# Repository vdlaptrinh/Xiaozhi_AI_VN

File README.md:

# Xiaozhi AI VN (`Xiaozhi_AI_VN`)

Kho lưu trữ mã nguồn, phần cứng và hướng dẫn cấu hình để tự build **Xiaozhi AI** phiên bản tiếng Việt sử dụng vi điều khiển ESP32-S3.

---

## 📂 Cấu trúc Repository

```text
Xiaozhi_AI_VN/
├── esp32s3_kit/         # Thiết kế phần cứng (KiCAD 10 project, có sẵn file xuất PCB PDF)
├── firmware/            # Chứa các file binary (.bin) biên dịch sẵn cho từng loại board
├── huong-dan-build-xiaozhi.md            # Hướng dẫn build xiaozhi
└── README.md            # Tài liệu giới thiệu dự án
```
---

1. Thư mục esp32s3_kit/
Phần cứng thiết kế: Dự án mạch phần cứng dùng KiCAD (phiên bản 10).

Tài liệu sản xuất: Đã hỗ trợ sẵn các file xuất PCB dưới dạng PDF giúp dễ dàng xem xét, in ấn hoặc đặt mạch (Gerber/PCB layout).

2. Thư mục firmware/
File Binary: Tổng hợp các file .bin sẵn sàng để flash trực tiếp lên các dòng board ESP32 hỗ trợ dự án.

Giúp người dùng có thể trải nghiệm nhanh chóng mà chưa cần tự build mã nguồn từ đầu.

🚀 File Hướng dẫn Build Firmware [click here](https://github.com/vdlaptrinh/Xiaozhi_AI_VN/blob/main/huong-dan-build-xiaozhi.md)
Chi tiết từng bước cách tự build firmware Xiaozhi AI tiếng Việt:

[X] Cài đặt môi trường phát triển (ESP-IDF / PlatformIO).

[X] Cấu hình kết nối Audio (I2S, Micro, Loa) và Wi-Fi/Server AI.

[X] Tiến hành biên dịch và nạp firmware (flash) vào ESP32-S3.

🤝 Đóng góp & Phát triển
Mọi đóng góp, báo lỗi (issue) hoặc thảo luận cải tiến phần cứng/phần mềm đều được hoan nghênh để hoàn thiện cộng đồng Xiaozhi AI tại Việt Nam!

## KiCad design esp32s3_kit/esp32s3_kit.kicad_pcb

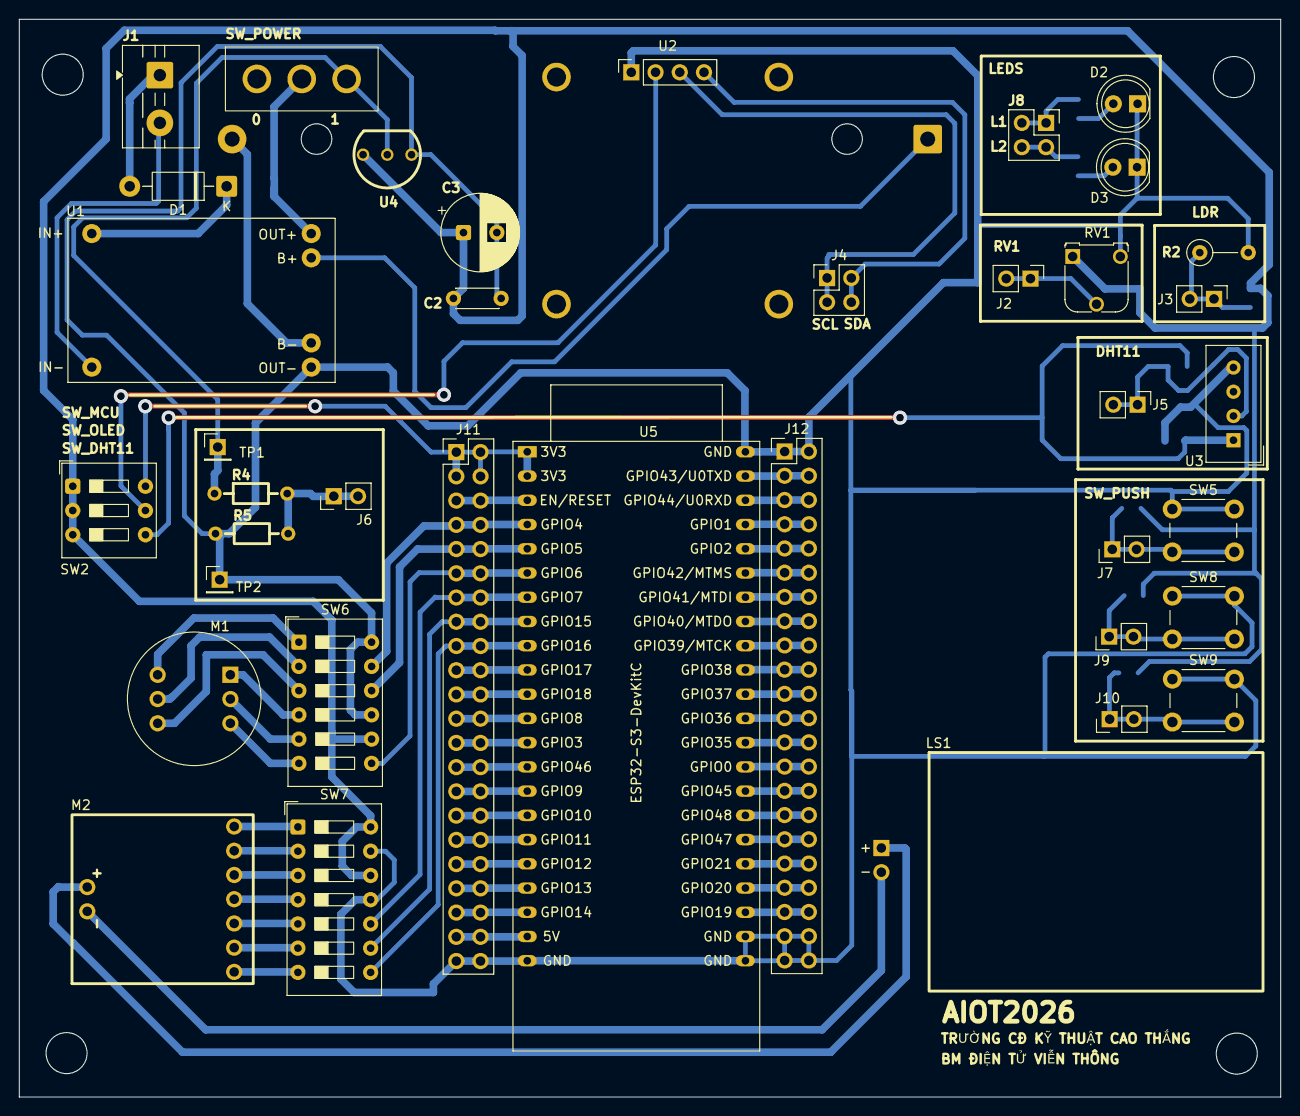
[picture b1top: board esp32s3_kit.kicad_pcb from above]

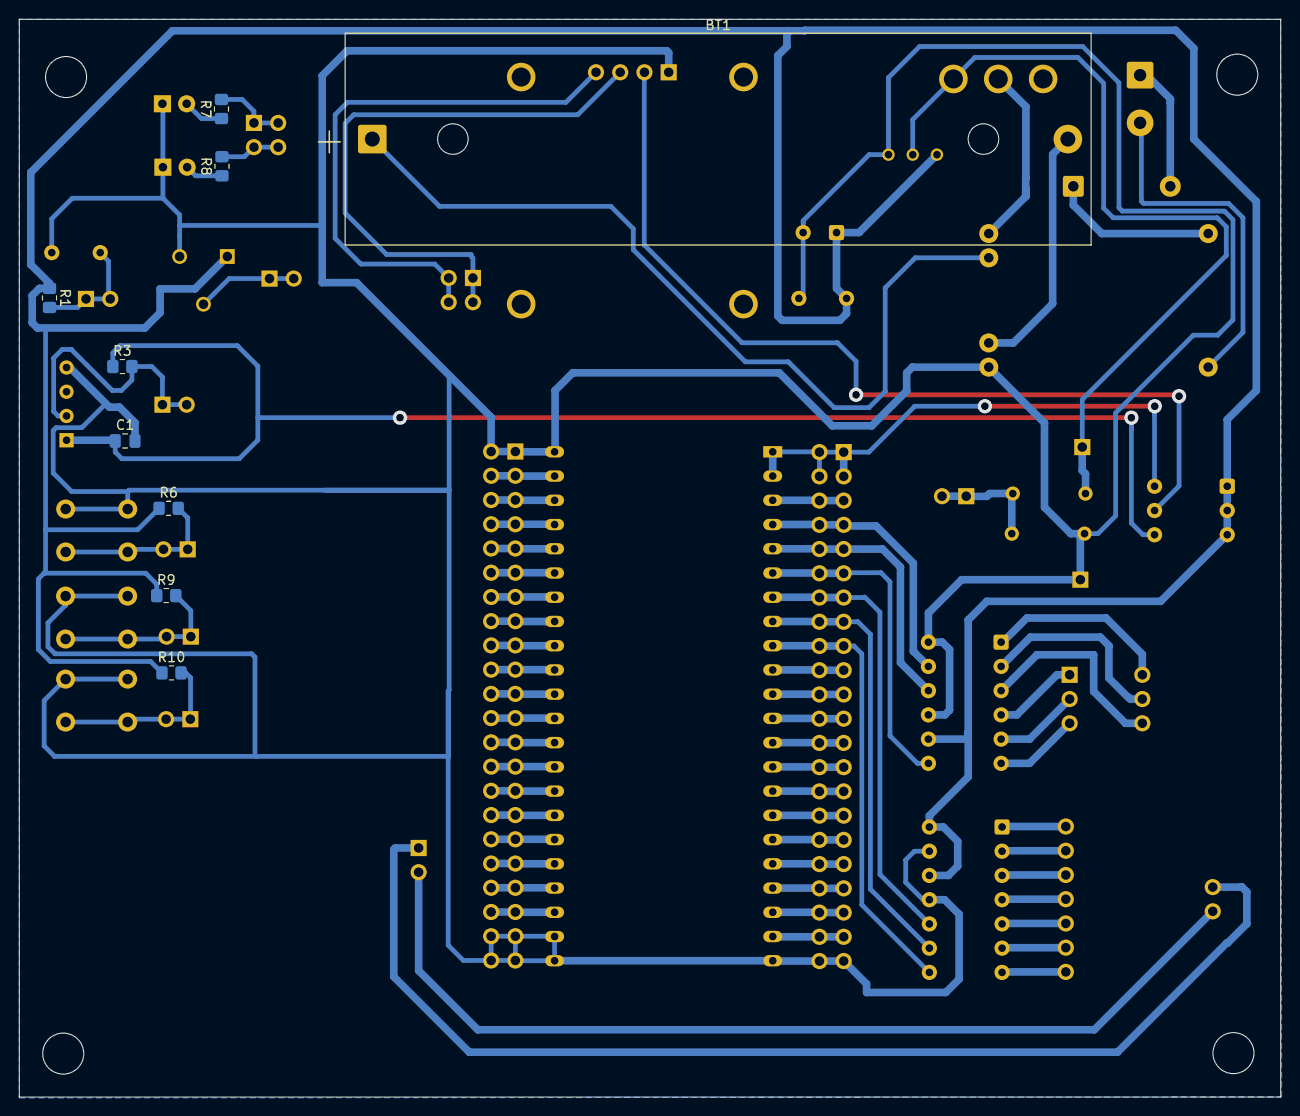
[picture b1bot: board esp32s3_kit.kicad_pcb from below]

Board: 2 copper layers, 132.2 x 112.9 mm, 47 parts (9 on the bottom side), 78 nets.

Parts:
BT1: Battery_Cell; BatteryHolder_MPD_BK-18650-PC2
C1: C; C_0805_2012Metric_Pad1.18x1.45mm_HandSolder
C2: C; C_Disc_D4.3mm_W1.9mm_P5.00mm
C3: C_US; CP_Radial_D8.0mm_P3.50mm
D1: 1N4001; D_DO-41_SOD81_P10.16mm_Horizontal
D2, D3: LED; LED_D5.0mm
J1: Screw_Terminal_01x02; TerminalBlock_MaiXu_MX126-5.0-02P_1x02_P5.00mm
J2, J3, J5, J6, J7, J9, J10: Conn_02x01; PinHeader_1x02_P2.54mm_Vertical
J4, J8: Conn_02x02_Top_Bottom; PinHeader_2x02_P2.54mm_Vertical
J11, J12: Conn_02x22_Top_Bottom; PinHeader_2x22_P2.54mm_Vertical_double
LS1: Speaker; speaker_2.5x3.5cm
M1: module_micro_inmp441; MODULE_MICRO_INMP441
M2: Module_MAX98357A
R1, R3, R6, R7, R8, R9, R10: R_US; R_0805_2012Metric_Pad1.20x1.40mm_HandSolder
R2: R_Photo; R_Axial_DIN0207_L6.3mm_D2.5mm_P5.08mm_Vertical
R4, R5: R_US; CFR25S
RV1: R_Potentiometer; Potentiometer_Runtron_RM-065_Vertical
SW1: SW_Wuerth_450301014042; SW_ss12d10
SW2: SW_DIP_x03; SW_DIP_SPSTx03_Slide_9.78x9.8mm_W7.62mm_P2.54mm
SW5, SW8, SW9: SW_Push; SW_PUSH_6mm_H7.3mm
SW6: SW_DIP_x06; SW_DIP_SPSTx06_Slide_9.78x17.42mm_W7.62mm_P2.54mm
SW7: SW_DIP_x07; SW_DIP_SPSTx07_Slide_9.78x19.96mm_W7.62mm_P2.54mm
TP1, TP2: TestPoint; PinHeader_1x01_P2.54mm_Vertical
U1: Module_TP4056; TP4056-Module
U2: Module_OLED_0.96; OLED_SSD1306_I2C_0.96
U3: DHT11; Aosong_DHT11_5.5x12.0_P2.54mm
U4: MCP1700x-330xxTO; 2SC1815_TO_92
U5: ESP32-S3-DevKitC

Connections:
+3V3: C2.1, C3.1, R1.1, R6.1, R9.1, R10.1, RV1.1, SW2.1, SW2.2, SW2.3, SW6.8, SW7.12, SW7.14, U4.3 (VO)
/5V: J11.21, J11.43, U5.21 (5V)
/DHT11: C1.1, R3.1, SW2.4, U3.1 (VDD)
/GPIO0: J12.14, J12.36, U5.31 (GPIO0)
/GPIO1: J12.4, J12.26, U5.41 (GPIO1/ADC1_CH0)
/GPIO2: J12.5, J12.27, U5.40 (GPIO2/ADC1_CH1)
/GPIO3: J11.13, J11.35, U5.13 (GPIO3/ADC1_CH2)
/GPIO4: J11.4, J11.26, SW6.11, U5.4 (GPIO4/ADC1_CH3)
/GPIO5: J11.5, J11.27, SW6.10, U5.5 (GPIO5/ADC1_CH4)
/GPIO6: J11.6, J11.28, SW6.7, U5.6 (GPIO6/ADC1_CH5)
/GPIO7: J11.7, J11.29, SW7.10, U5.7 (GPIO7/ADC1_CH6)
/GPIO8: J11.12, J11.34, U5.12 (GPIO8/ADC1_CH7)
/GPIO9: J11.15, J11.37, U5.15 (GPIO9/ADC1_CH8)
/GPIO10: J11.16, J11.38, U5.16 (GPIO10/ADC1_CH9)
/GPIO11: J11.17, J11.39, U5.17 (GPIO11/ADC2_CH0)
/GPIO12: J11.18, J11.40, U5.18 (GPIO12/ADC2_CH1)
/GPIO13: J11.19, J11.41, U5.19 (GPIO13/ADC2_CH2)
/GPIO14: J11.20, J11.42, U5.20 (GPIO14/ADC2_CH3)
/GPIO15: J11.8, J11.30, SW7.9, U5.8 (GPIO15/ADC2_CH4/32K_P)
/GPIO16: J11.9, J11.31, SW7.8, U5.9 (GPIO16/ADC2_CH5/32K_N)
/GPIO17: J11.10, J11.32, U5.10 (GPIO17/ADC2_CH6)
/GPIO18: J11.11, J11.33, U5.11 (GPIO18/ADC2_CH7)
/GPIO19: J12.20, J12.42, U5.25 (GPIO19/USB_D-)
/GPIO20: J12.19, J12.41, U5.26 (GPIO20/USB_D+)
/GPIO21: J12.18, J12.40, U5.27 (GPIO21)
/GPIO35: J12.13, J12.35, U5.32 (GPIO35)
/GPIO36: J12.12, J12.34, U5.33 (GPIO36)
/GPIO37: J12.11, J12.33, U5.34 (GPIO37)
/GPIO38: J12.10, J12.32, U5.35 (GPIO38)
/GPIO39: J12.9, J12.31, U5.36 (GPIO39/MTCK)
/GPIO40: J12.8, J12.30, U5.37 (GPIO40/MTDO)
/GPIO41: J12.7, J12.29, U5.38 (GPIO41/MTDI)
/GPIO42: J12.6, J12.28, U5.39 (GPIO42/MTMS)
/GPIO45: J12.15, J12.37, U5.30 (GPIO45)
/GPIO46: J11.14, J11.36, U5.14 (GPIO46)
/GPIO47: J12.17, J12.39, U5.28 (GPIO47)
/GPIO48: J12.16, J12.38, U5.29 (GPIO48)
/MCU: J11.1, J11.2, J11.23, J11.24, SW2.6, U5.1 (3V3), U5.2 (3V3)
/OLED: SW2.5, U2.2 (VDD)
/RST: J11.3, J11.25, U5.3 (CHIP_PU)
/RX: J12.3, J12.25, U5.42 (GPIO44/U0RXD)
/TX: J12.2, J12.24, U5.43 (GPIO43/U0TXD)
GND: C1.2, C2.2, C3.2, D2.1 (K), D3.1 (K), J11.22, J11.44, J12.1, J12.21, J12.22, J12.23, J12.43, J12.44, R2.2, R5.2, RV1.3, SW5.1, SW6.9, SW6.12, SW7.11, SW7.13, SW8.1, SW9.1, TP2.1 (1_1), U1.4 (VOUT-), U2.1 (GND), U3.4 (GND), U4.1 (GND), U5.22 (GND), U5.23 (GND), U5.24 (GND), U5.44 (GND)
unnamed: BT1.1 (+), U1.5 (B^{+})
unnamed: BT1.2 (-), U1.6 (B-)
unnamed: D1.2 (A), J1.1
unnamed: D1.1 (K), U1.1 (V_{IN})
unnamed: D2.2 (A), R7.1
unnamed: D3.2 (A), R8.1
unnamed: J1.2, U1.2 (VIN^{-})
unnamed: J2.1, J2.2, RV1.2
unnamed: J3.1, J3.2, R1.2, R2.1
unnamed: J4.1, J4.3, U2.3 (SCK)
unnamed: J4.2, J4.4, U2.4 (SDA)
unnamed: J5.1, J5.2, R3.2, U3.2 (DATA)
unnamed: J6.1, J6.2, R4.2, R5.1
unnamed: J7.1, J7.2, R6.2, SW5.2
unnamed: J8.1, J8.3, R7.2
unnamed: J8.2, J8.4, R8.2
unnamed: J9.1, J9.2, R9.2, SW8.2
unnamed: J10.1, J10.2, R10.2, SW9.2
unnamed: M1.1, SW6.1
unnamed: M1.2, SW6.2
unnamed: M1.3, SW6.3
unnamed: M1.4, SW6.4
unnamed: M1.5, SW6.5
unnamed: M1.6, SW6.6
unnamed: LS1.1, M2.8 (+SPK)
unnamed: LS1.2, M2.9 (-SPK)
unnamed: M2.6 (BCLK), SW7.6
unnamed: M2.5 (DIN), SW7.5
unnamed: M2.4 (GAIN), SW7.4
unnamed: M2.2 (GND), SW7.2
unnamed: M2.7 (LRC), SW7.7
unnamed: M2.3 (SD), SW7.3
unnamed: M2.1 (VIN), SW7.1
unnamed: SW1.2 (B), U1.3 (V_{OUT})
V_BAT: R4.1, SW1.3 (C), TP1.1 (1_1), U4.2 (VI)
